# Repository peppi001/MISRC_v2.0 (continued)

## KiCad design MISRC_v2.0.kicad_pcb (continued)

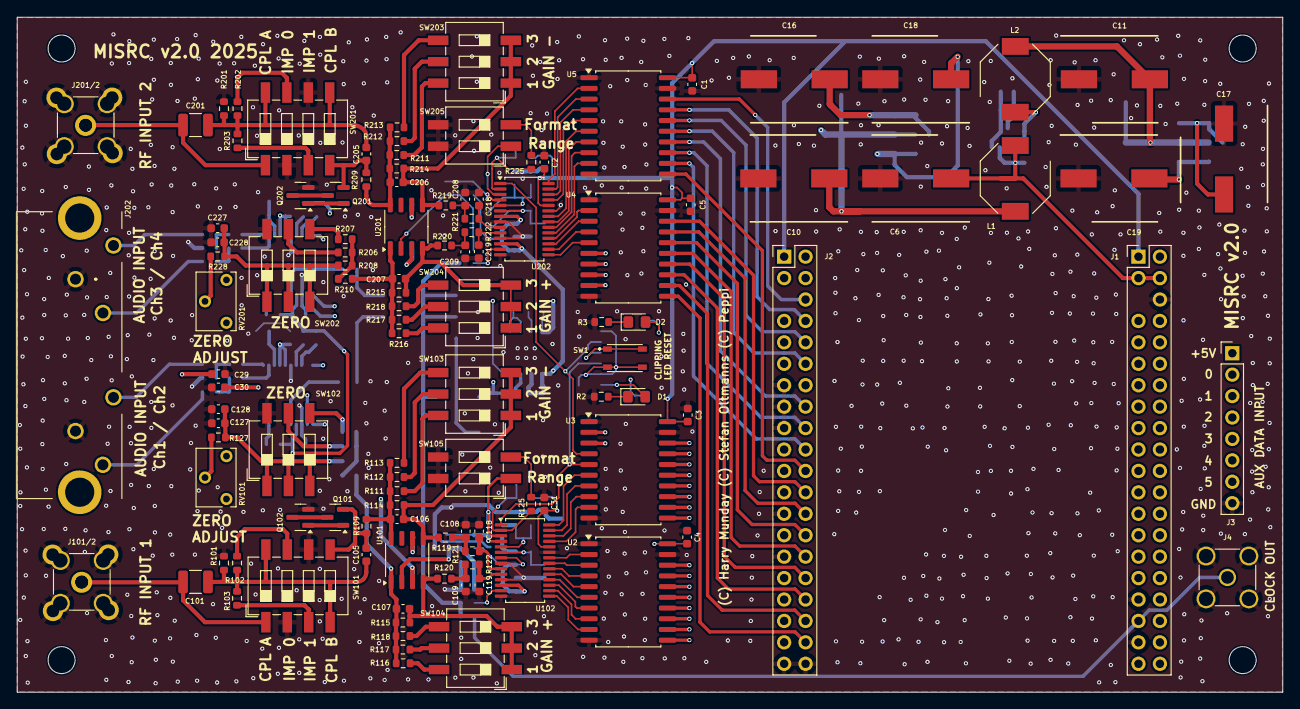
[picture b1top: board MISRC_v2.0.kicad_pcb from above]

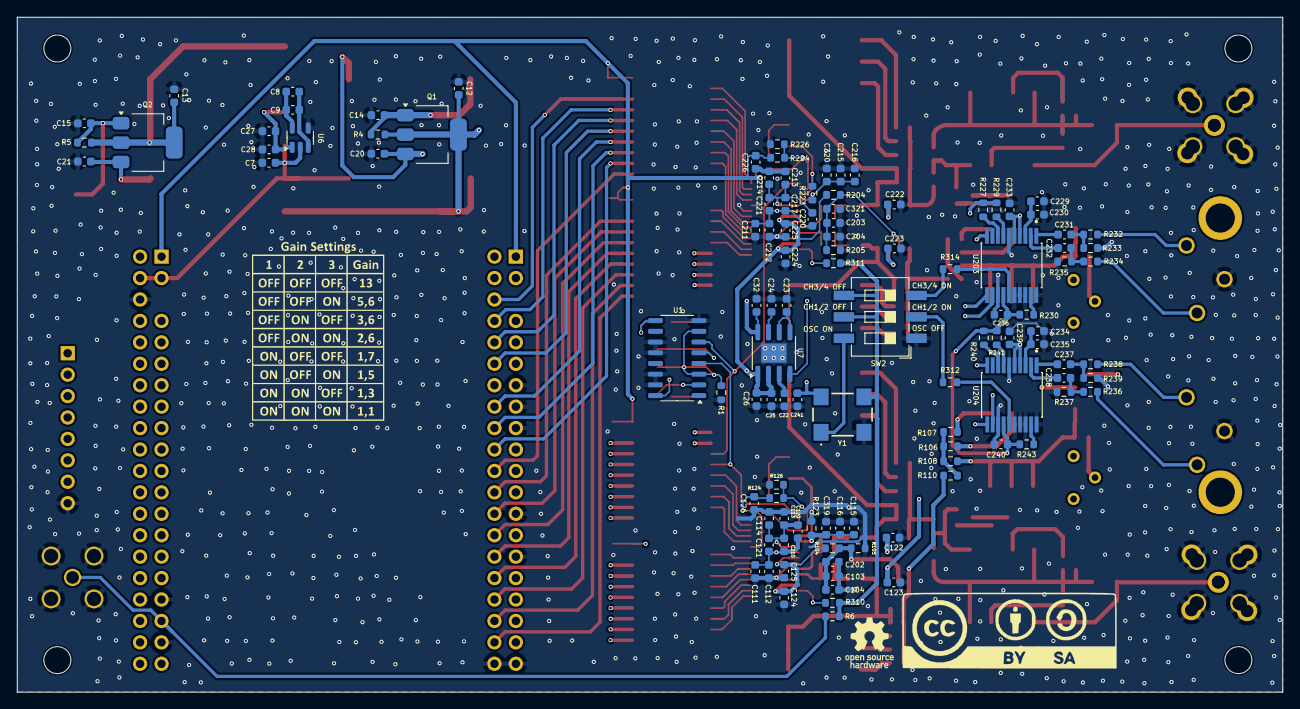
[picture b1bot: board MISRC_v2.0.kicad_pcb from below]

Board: 4 copper layers, 150.0 x 80.0 mm, 233 parts (114 on the bottom side), 180 nets.

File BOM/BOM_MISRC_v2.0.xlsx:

Reference | Value | Footprint | Qty | DNP | Manufacturer_Part_Number
C1,C2,C3,C4,C5,C7,C12,C13,C20,C21,C22,C23,C24,C29,C30,C31,C231,C232,C237,C238,C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 | 1u | Capacitor_SMD:C_0603_1608Metric | 21 |  | GRM188D71H105KE01D
C6 | 470u | Footprints:CAPAE1030X850N | 1 |  | UCL1C471MCL6GS
C8,C25,C28,C32,C127,C202,C210,C217,C227,C229,C234,C319,C320,C321 | 10u | Capacitor_SMD:C_0603_1608Metric | 14 |  | GRM188C81C106MA73D
C9,C14,C15,C26,C103,C112,C113,C115,C120,C122,C123,C124,C125,C126,C203,C212,C213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 | 100n | Capacitor_SMD:C_0603_1608Metric | 30 |  | GRM188R72A104KA35D
C10,C11,C16,C17,C18,C19 | 470u | Footprints:CAPAE1030X850N | 6 |  | UCL1C471MCL6GS
C27,C104,C111,C114,C116,C121,C128,C204,C211,C214,C216,C221,C228 | 1n/1 | Capacitor_SMD:C_0603_1608Metric | 13 |  | GCM1885C1H102FA16D
C101,C201 | 100u | Capacitor_SMD:C_1210_3225Metric | 2 |  | GRM32ER61A107ME20K
C105,C205 | 470n/1 | Capacitor_SMD:C_0603_1608Metric | 2 |  | GRM188R71E474KA12D
C106,C107,C206,C207 | 1p | Capacitor_SMD:C_0603_1608Metric | 4 | DNP
C108,C109,C208,C209 | 82pF/1 | Capacitor_SMD:C_0603_1608Metric | 4 |  | GRM1885C1H820GA01D
C118,C119,C218,C219 | 15pF/1 | Capacitor_SMD:C_0603_1608Metric | 4 |  | GRM1885C1H150JA01J
D1,D2 | LED | LED_SMD:LED_0805_2012Metric_Pad1.15x1.40mm_HandSolder | 2 |  | APT2012EC
H1,H2,H3,H4 | MountingHole | MountingHole:MountingHole_3.2mm_M3 | 4 | DNP
H5 | MISRC-Gain_Settings | Footprints:MISRC_gain_settings | 1 | DNP
H6 | CC Licence | Footprints:CC Licence | 1 | DNP
H7 | OSHW Logo | Symbol:OSHW-Logo_5.7x6mm_SilkScreen | 1 | DNP
J1 | GPIFII_J6 | Footprints:PinHeader_2x20_P2.54mm_Vertical-1 | 1 |  | 61302021121
J2 | GPIFII_J7 | Footprints:PinHeader_2x20_P2.54mm_Vertical-1 | 1 |  | 61302021121
J3 | Conn_01x08_Socket | Connector_PinHeader_2.54mm:PinHeader_1x08_P2.54mm_Vertical | 1 |  | 61300811121
J4 | Conn_01x01_Shielded | Footprints:SMA_Amphenol_901-144_Vertical2 | 1 |  | RF2-04A-T-00-50-G
J101,J201 | BNC_Rosenberger | Footprints:BNC_Right_Angle-DOSIN-801-0050_5pin | 2 |  | DOSIN-801-0050
J101/2,J201/2 | Conn_01x01_Shielded | Footprints:SMA_Amphenol_901-144_Horizontal | 2 | DNP | CONSMA002-L-G
J202 | KLP42X-61-WW_RR | Footprints:KLP42X61WWRR | 1 |  | KLP42X-61-WW/RR
L1,L2 | 100u | Footprints:L_Bourns-SRU8043_2 | 2 |  | SRU8043-101Y
Q1 | FZT690B | Package_TO_SOT_SMD:SOT-223-3_TabPin2 | 1 |  | FZT690BTA
Q2 | FZT790A | Package_TO_SOT_SMD:SOT-223-3_TabPin2 | 1 |  | FZT790A
Q101,Q102,Q201,Q202 | CMPT5179 | Footprints:SOT-23 | 4 |  | CMPT5179 TR PBFREE
R1,R123,R126,R223,R226,R232,R234,R236,R238 | 10k | Resistor_SMD:R_0603_1608Metric | 9 |  | RC0603FR-0710KL
R2,R3 | 100 | Resistor_SMD:R_0603_1608Metric | 2 |  | RC0603FR-07100RL
R4,R5,R227,R229,R230,R240,R241,R243 | 1k | Resistor_SMD:R_0603_1608Metric | 8 |  | RC0603FR-071KL
R6,R310,R311,R312,R314 | 0R | Resistor_SMD:R_0603_1608Metric | 5 |  | RC0603FR-070RL
R101,R103,R106,R201,R203,R206 | 75B | Resistor_SMD:R_0603_1608Metric | 6 |  | RC0603FR-1075RL
R102,R202 | 150B | Resistor_SMD:R_0603_1608Metric | 2 |  | RC0603FR-07150RL
R104,R105,R111,R116,R204,R205,R211,R216 | 1kB | Resistor_SMD:R_0603_1608Metric | 8 |  | RC0603FR-071KL
R107,R108,R207,R208 | 39B | Resistor_SMD:R_0603_1608Metric | 4 |  | RC0603FR-0739RL
R109,R110,R209,R210 | 499B | Resistor_SMD:R_0603_1608Metric | 4 |  | RC0603FR-07499RL
R112,R117,R212,R217 | 2k49B | Resistor_SMD:R_0603_1608Metric | 4 |  | RC0603FR-072K49L
R113,R118,R213,R218 | 4k99B | Resistor_SMD:R_0603_1608Metric | 4 |  | RC0603FR-074K99L
R114,R115,R214,R215 | 6k49B | Resistor_SMD:R_0603_1608Metric | 4 |  | RC0603FR-136K49L
R119,R120,R219,R220 | 40B | Resistor_SMD:R_0603_1608Metric | 4 |  | RC0603FR-0739R2L
R121,R122,R221,R222 | 22B | Resistor_SMD:R_0603_1608Metric | 4 |  | RC0603FR-0722RL
R124,R224 | 4k99 | Resistor_SMD:R_0603_1608Metric | 2 |  | RC0603FR-074K99L
R125,R127,R225,R228 | 3k3 | Resistor_SMD:R_0603_1608Metric | 4 |  | RC0603FR-133K3L
R233,R235,R237,R239 | 47k | Resistor_SMD:R_0603_1608Metric | 4 |  | RC0603FR-0747KL
RV101,RV201 | 10k | Potentiometer_THT:Potentiometer_Bourns_3266W_Vertical | 2 |  | 3266W-1-103LF
SW1 | PTS810SJM250SMTRLFS | Footprints:PTS810SJG250SMTRLFS | 1 |  | PTS810SJM250SMTRLFS
SW2,SW102,SW103,SW104,SW202,SW203,SW204 | SW_DIP_x03 | Button_Switch_SMD:SW_DIP_SPSTx03_Slide_6.7x9.18mm_W8.61mm_P2.54mm_LowProfile | 7 |  | A6S-3104-H
SW101,SW201 | SW_DIP_x04 | Button_Switch_SMD:SW_DIP_SPSTx04_Slide_6.7x11.72mm_W8.61mm_P2.54mm_LowProfile | 2 |  | IKD0403101
SW105,SW205 | SW_DIP_x02 | Button_Switch_SMD:SW_DIP_SPSTx02_Slide_6.7x6.64mm_W8.61mm_P2.54mm_LowProfile | 2 |  | IKD0203101
U1 | 4043 | Package_SO:SO-16_3.9x9.9mm_P1.27mm | 1 |  | HEF4043BT-Q100J
U2,U3,U4,U5 | 74VHC541 | Package_SO:SOIC-20W_7.5x12.8mm_P1.27mm | 4 |  | 74VHC541D,118
U6 | TPS60401 | Footprints:SOT-23-5 | 1 |  | TPS60401DBVT
U7 | ADP7156ARDZ | Footprints:SOIC-8-1EP_3.9x4.9mm_P1.27mm_EP2.29x3mm_2 | 1 |  | ADP7156ARDZ-3.3-R7
U101,U201 | AD8138ARZ | Package_SO:SO-8_3.9x4.9mm_P1.27mm | 2 |  | AD8138ARZ
U102,U202 | AD9235 | Package_SO:TSSOP-28_4.4x9.7mm_P0.65mm | 2 |  | AD9235BRUZ-40
U203,U204 | PCM1802DBR | Footprints:SOP65P780X200-20N | 2 |  | PCM1802DBR
Y1 | CB3LV-5I-40M0000 | Footprints:CB3LV5I40M0000 | 1 |  | CB3LV-5I-40M0000

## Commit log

2025-04-04 Add tang nano20k 3D model
